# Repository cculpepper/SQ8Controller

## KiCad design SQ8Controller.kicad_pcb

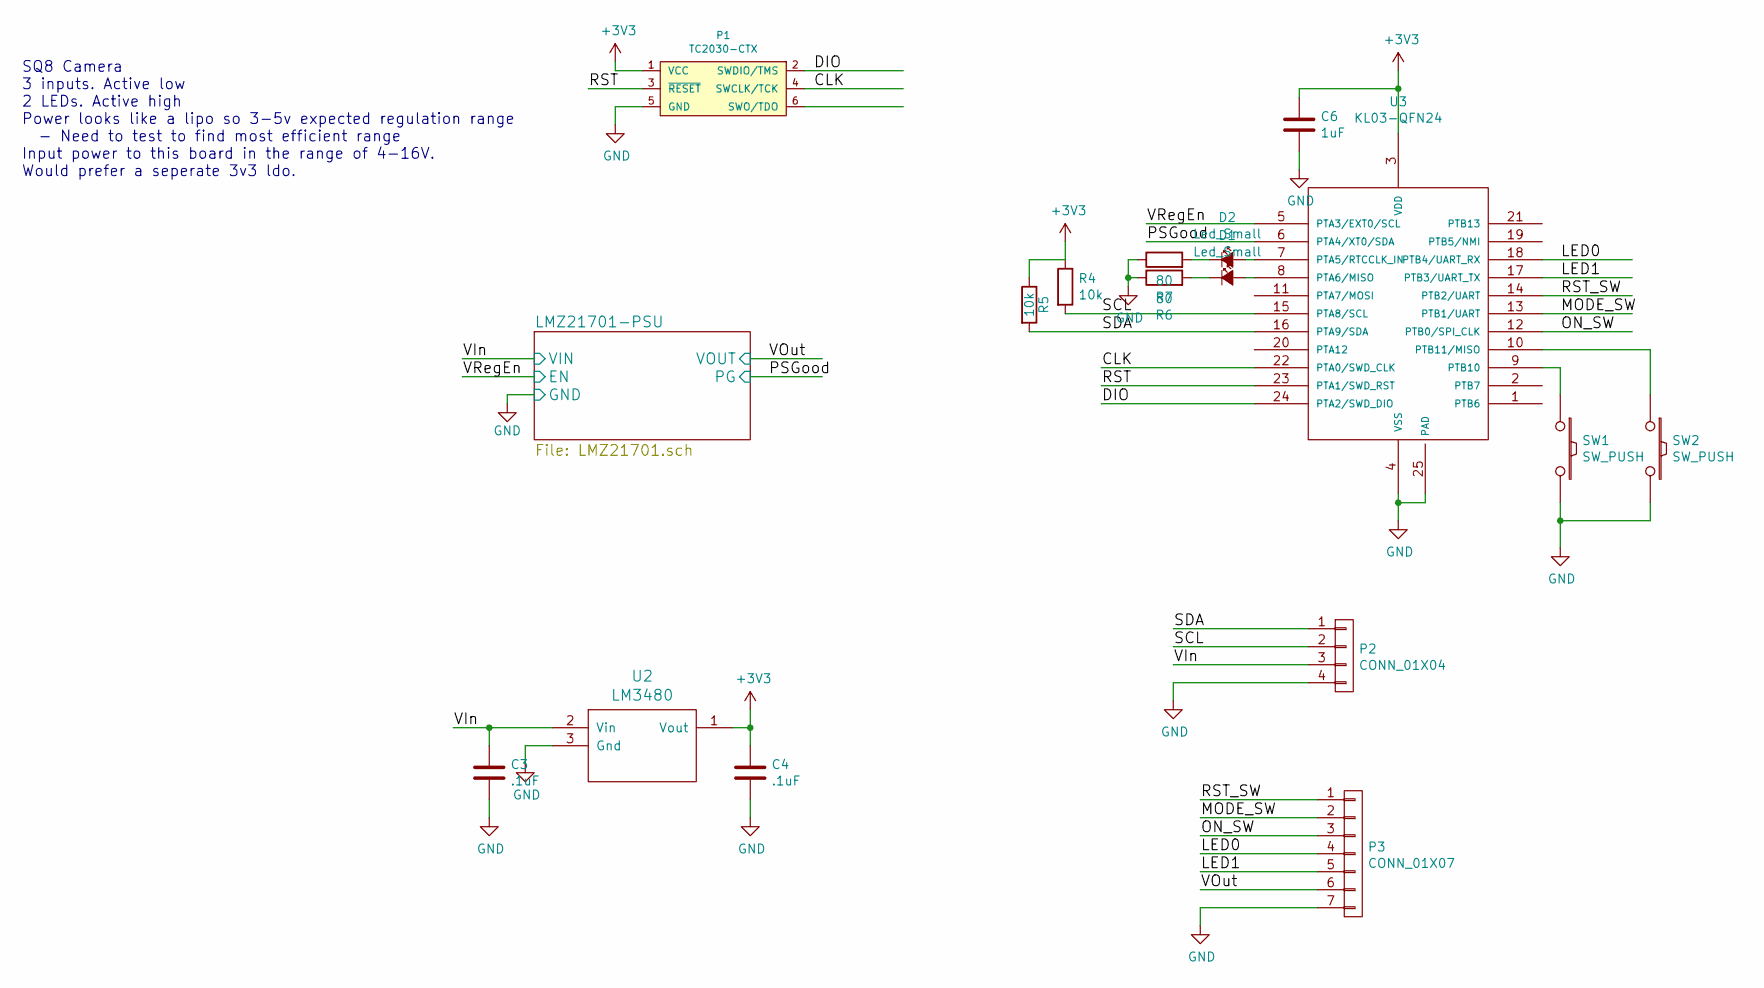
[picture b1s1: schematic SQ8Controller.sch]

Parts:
C3, C4: .1uF; C_0603
C6: 1uF; C_0603
D1, D2: Led_Small; LED-0603
P1: TC2030-CTX; TC2030-MCP-NL
P2: CONN_01X04; duraclik-4
P3: CONN_01X07; duraclik-7
R4, R5: 10k; R_0603
R6, R7: 80; R_0603
SW1, SW2: SW_PUSH; B3U-1000P; Manufacturer PN B3U-1000P
U2: LM3480; SOT-23
U3: KL03-QFN24; qfn-24

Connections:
+3V3: C4.1, C6.1, P1.1 (VCC), R4.1, R5.1, U2.1 (Vout), U3.3 (VDD)
/CLK: P1.4 (SWCLK/TCK), U3.22 (PTA0/SWD_CLK)
/DIO: P1.2 (SWDIO/TMS), U3.24 (PTA2/SWD_DIO)
/LED0: P3.4, U3.18 (PTB4/UART_RX)
/LED1: P3.5, U3.17 (PTB3/UART_TX)
/MODE_SW: P3.2, U3.13 (PTB1/UART)
/ON_SW: P3.3, U3.12 (PTB0/SPI_CLK)
/PSGood: U3.6 (PTA4/XT0/SDA); also elsewhere on the board
/RST: P1.3 (~RESET~), U3.23 (PTA1/SWD_RST)
/RST_SW: P3.1, U3.14 (PTB2/UART)
/SCL: P2.2, R4.2, U3.15 (PTA8/SCL)
/SDA: P2.1, R5.2, U3.16 (PTA9/SDA)
/VIn: C3.1, P2.3, U2.2 (Vin); also elsewhere on the board
/VOut: P3.6; also elsewhere on the board
/VRegEn: U3.5 (PTA3/EXT0/SCL); also elsewhere on the board
GND: C3.2, C4.2, C6.2, P1.5 (GND), P2.4, P3.7, R6.1, R7.1, SW1.2, SW2.2, U2.3 (Gnd), U3.4 (VSS), U3.25 (PAD); also elsewhere on the board
unnamed: D1.1 (K), R6.2
unnamed: D1.2 (A), U3.8 (PTA6/MISO)
unnamed: D2.1 (K), R7.2
unnamed: D2.2 (A), U3.7 (PTA5/RTCCLK_IN)
unnamed: SW1.1, U3.9 (PTB10)
unnamed: SW2.1, U3.10 (PTB11/MISO)

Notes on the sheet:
SQ8 Camera 3 inputs. Active low 2 LEDs. Active high Power looks like a lipo so 3-5v expected regulation range - Need to test to find most efficient range Input power to this board in the range of 4-16V. Would prefer a seperate 3v3 ldo.

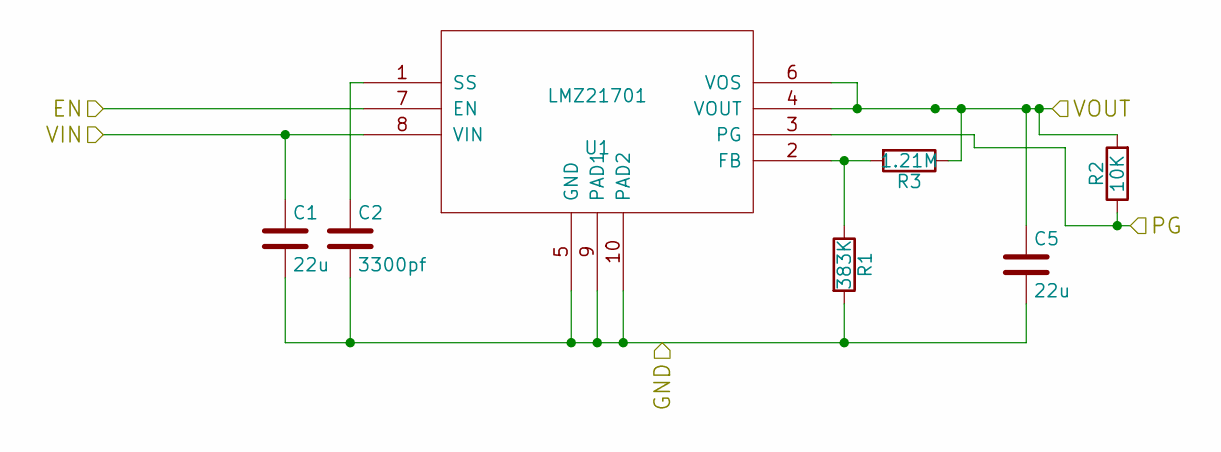
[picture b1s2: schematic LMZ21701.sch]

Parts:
C1, C5: 22u; C_0805
C2: 3300pf; C_0603
R1: 383K; R_0603
R2: 10K; R_0603
R3: 1.21M; R_0603
U1: LMZ21701; MicroSIP; Manufacturer PN LMZ21700SILT

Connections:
/PSGood: R2.1, U1.3 (PG); also elsewhere on the board
/VIn: C1.1, U1.8 (VIN); also elsewhere on the board
/VOut: C5.1, R2.2, R3.1, U1.4 (VOUT), U1.6 (VOS); also elsewhere on the board
/VRegEn: U1.7 (EN); also elsewhere on the board
GND: C1.2, C2.2, C5.2, R1.2, U1.5 (GND), U1.9 (PAD1), U1.10 (PAD2); also elsewhere on the board
unnamed: C2.1, U1.1 (SS)
unnamed: R1.1, R3.2, U1.2 (FB)

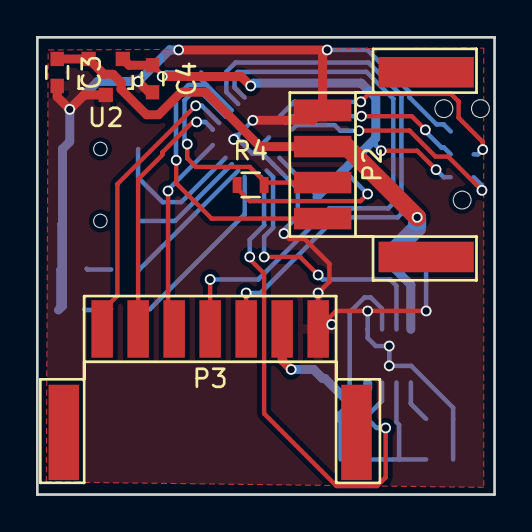
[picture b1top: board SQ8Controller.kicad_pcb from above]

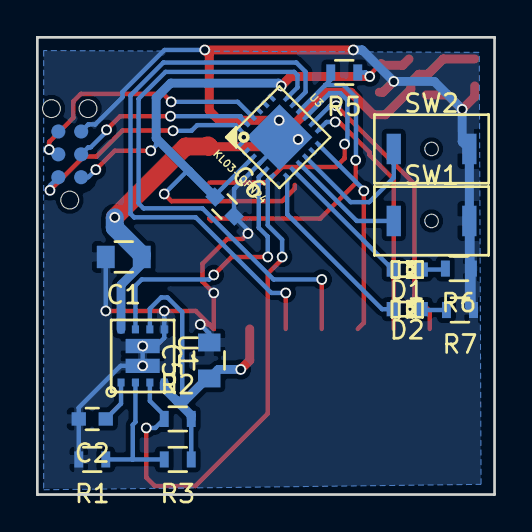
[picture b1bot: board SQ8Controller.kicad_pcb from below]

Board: 2 copper layers, 25.4 x 25.4 mm, 23 parts (17 on the bottom side), 24 nets.
